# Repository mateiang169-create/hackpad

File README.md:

# My RP2040 Hackpad

Welcome to the official documentation of my custom-built, open-source macro pad. This project was conceptualized, designed, and assembled from scratch as part of the Hack Club Stardance challenge. It combines a compact hardware footprint with highly customizable firmware to streamline daily developer workflows, shortcuts, and gaming macros.

---

## 📋 Table of Contents
- [Project Overview](#project-overview)
- [Key Features & Hardware Architecture](#key-features--hardware-architecture)
- [Repository Structure & File Organization](#repository-structure--file-organization)
- [Deep Dive: Design & Engineering Process](#deep-dive-design--engineering-process)
  - [1. Schematic Capture & PCB Routing (KiCad)](#1-schematic-capture--pcb-routing-kicad)
  - [2. 3D Enclosure Engineering (Autodesk Fusion 360)](#2-3d-enclosure-engineering-autodesk-fusion-360)
- [Step-by-Step Assembly & Getting Started Guide](#step-by-step-assembly--getting-started-guide)
- [License & Acknowledgments](#license--acknowledgments)

---

## 🔍 Project Overview
The primary goal of this project was to design a functional, aesthetically pleasing, and ergonomic macro pad that integrates physical tactile inputs with real-time visual feedback. Built around the powerful and versatile **Seeed Studio XIAO RP2040**, the board features a matrix of mechanical switches, an incremental rotary encoder for dynamic volume control or scrolling, and an I2C-enabled OLED display to render custom text, states, or animations on the fly.

---

## ✨ Key Features & Hardware Architecture
- **Core Processing Unit:** Powered by the dual-core ARM Cortex-M0+ RP2040 microcontroller running at up to 133 MHz, providing ample processing power and flexible Programmable I/O (PIO) capabilities.
- **Input Matrix:** Features 4 mechanical switch sockets wired in a custom matrix topology protected by 1N4148 switching diodes to eliminate ghosting and phantom presses during simultaneous inputs.
- **Rotary Control:** Integrates an EC11 incremental rotary encoder with an integrated push-button switch, ideal for multi-function controls (e.g., zooming, scrubbing timelines, or adjusting system audio levels).
- **Visual Feedback Display:** Equipped with a 0.91-inch SSD1306 monochrome OLED screen communicating via I2C protocol, offering crisp textual or graphical indicators.
- **Custom Enclosure:** A robust 3D-printed chassis engineered with a designated transparent viewing window (utilizing clear PETG or PLA filament) to showcase the internal soldered components and PCB traces.

---

## 📂 Repository Structure & File Organization
To maintain a clean and professional workflow compliant with hardware open-source standards, the repository is structured into distinct, dedicated directories:

├── CAD/              # Contains 3D computer-aided design files, step models, and fusion assemblies
├── Firmware/         # Contains source code, configuration scripts, and compiled binaries for the RP2040
├── PCB/              # Contains KiCad schematic (.sch/.kicad_sch), layout (.kicad_pcb), and project files
└── production/       # Contains manufacturing outputs, Gerber files, drill files, and BOM exports for fabrication

## Project Screenshots

### 3D PCB View

### Schematic

### PCB Design

### 3D Case

---

## Bill of Materials (BOM)

| Component | Quantity | Description |
| :--- | :---: | :--- |
| Seeed Studio XIAO RP2040 | 1 | Microcontroller |
| Mechanical Switches | 4 | Key switches |
| EC11 Rotary Encoder | 1 | Knob encoder |
| 0.91" OLED Screen (SSD1306) | 1 | Display |
| 1N4148 Diodes | 4 | Matrix diodes |
| 3D Printed Case | 1 | Custom enclosure |

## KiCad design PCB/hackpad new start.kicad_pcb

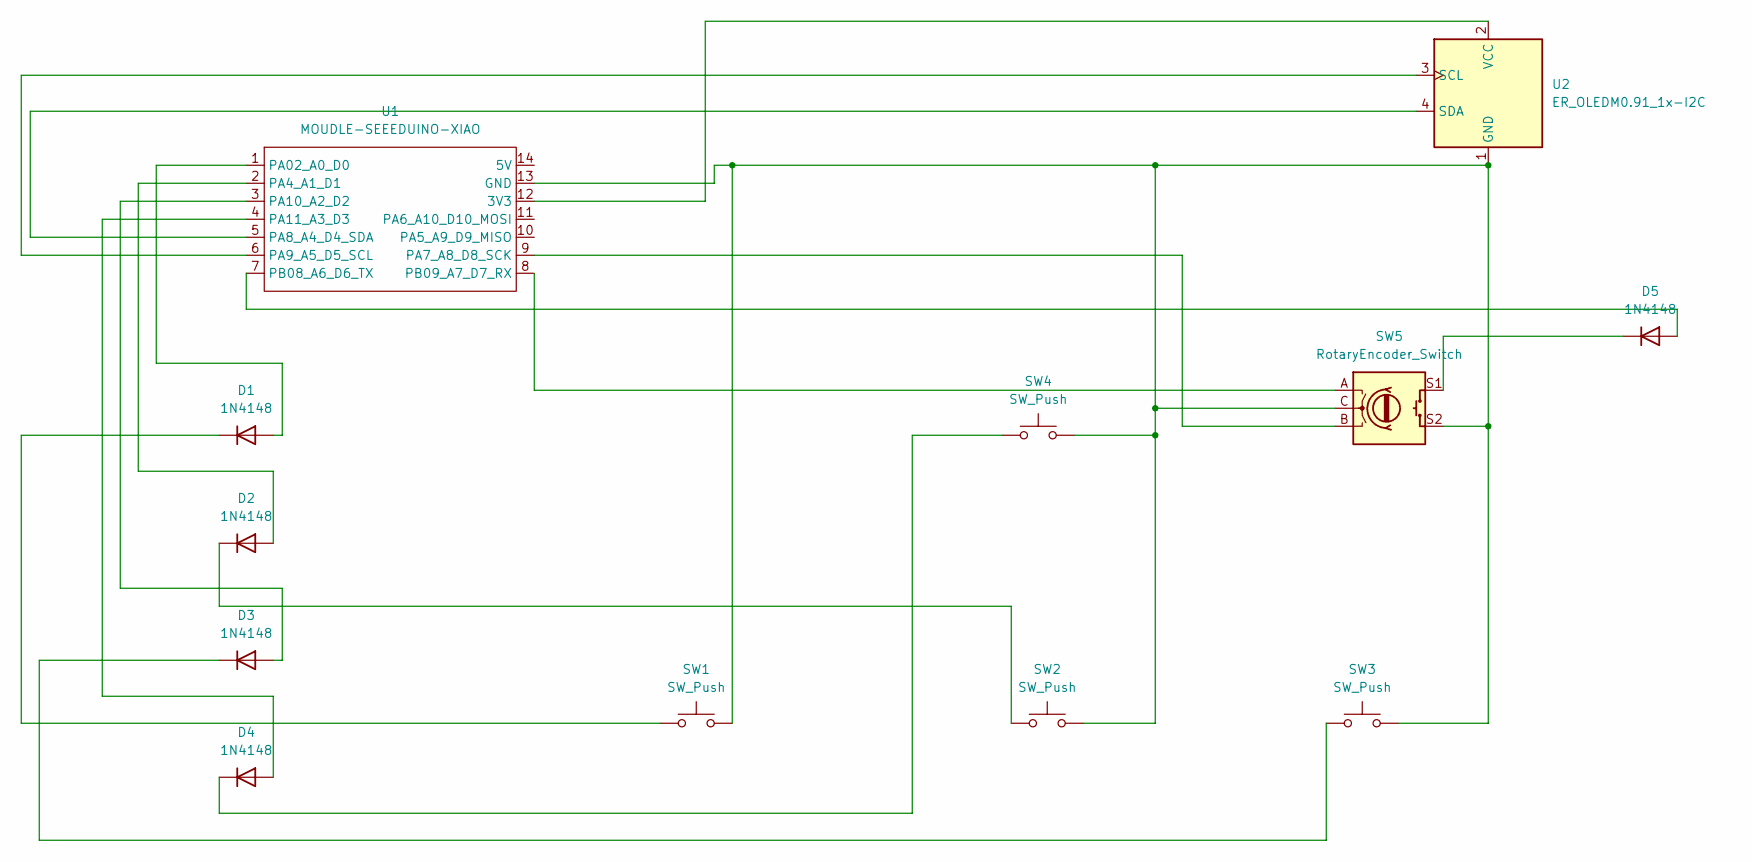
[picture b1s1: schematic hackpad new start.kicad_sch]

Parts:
D1, D2, D3, D4, D5: 1N4148; D_DO-35_SOD27_P7.62mm_Horizontal
SW1, SW2, SW3, SW4: SW_Push; SW_Cherry_MX_1.00u_Plate
SW5: RotaryEncoder_Switch; RotaryEncoder_Alps_EC11E-Switch_Vertical_H20mm
U1: MOUDLE-SEEEDUINO-XIAO; XIAO-Generic-Hybrid-14P-2.54-21X17.8MM
U2: ER_OLEDM0.91_1x-I2C

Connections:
unnamed: D1.2 (A), U1.1 (PA02_A0_D0)
unnamed: D1.1 (K), SW1.1
unnamed: D2.2 (A), U1.2 (PA4_A1_D1)
unnamed: D2.1 (K), SW2.1
unnamed: D3.2 (A), U1.3 (PA10_A2_D2)
unnamed: D3.1 (K), SW3.1
unnamed: D4.2 (A), U1.4 (PA11_A3_D3)
unnamed: D4.1 (K), SW4.1
unnamed: D5.2 (A), U1.7 (PB08_A6_D6_TX)
unnamed: D5.1 (K), SW5.S1
unnamed: U1.12 (3V3), U2.2 (VCC)
unnamed: SW1.2, SW2.2, SW3.2, SW4.2, SW5.C, SW5.S2, U1.13 (GND), U2.1 (GND)
unnamed: SW5.B, U1.9 (PA7_A8_D8_SCK)
unnamed: U1.5 (PA8_A4_D4_SDA), U2.4 (SDA)
unnamed: U1.6 (PA9_A5_D5_SCL), U2.3 (SCL)
unnamed: SW5.A, U1.8 (PB09_A7_D7_RX)

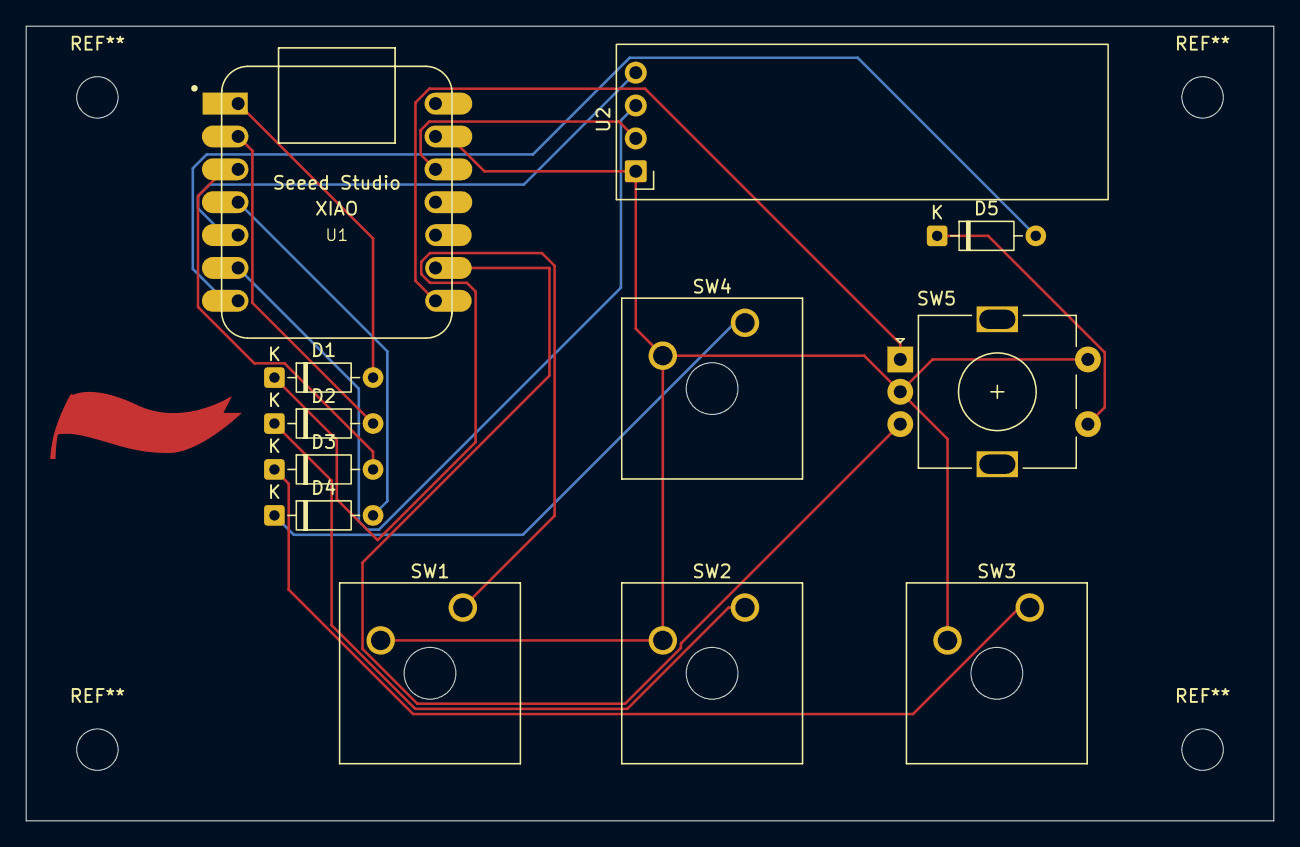
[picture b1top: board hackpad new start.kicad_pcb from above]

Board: 2 copper layers, 96.4 x 61.4 mm, 12 parts (0 on the bottom side), 16 nets.
